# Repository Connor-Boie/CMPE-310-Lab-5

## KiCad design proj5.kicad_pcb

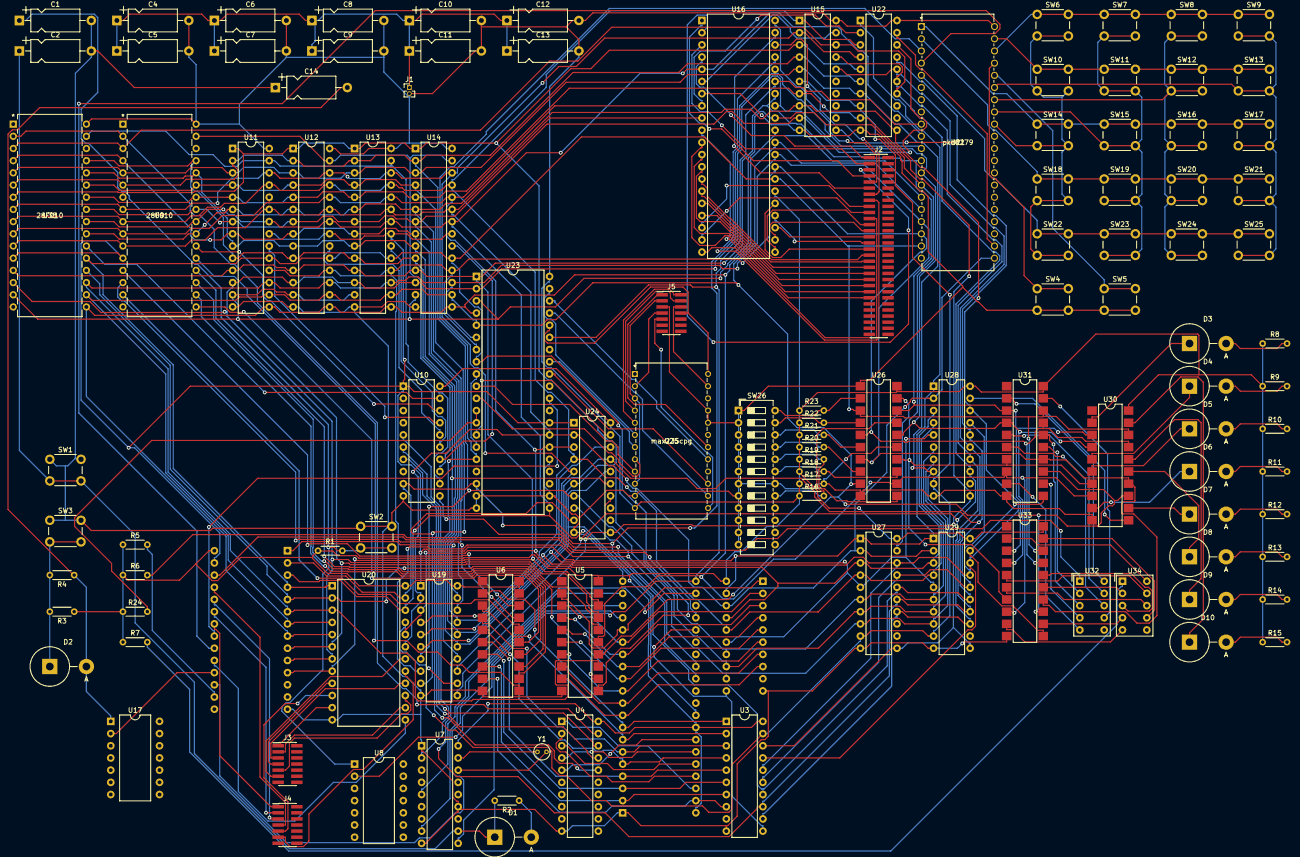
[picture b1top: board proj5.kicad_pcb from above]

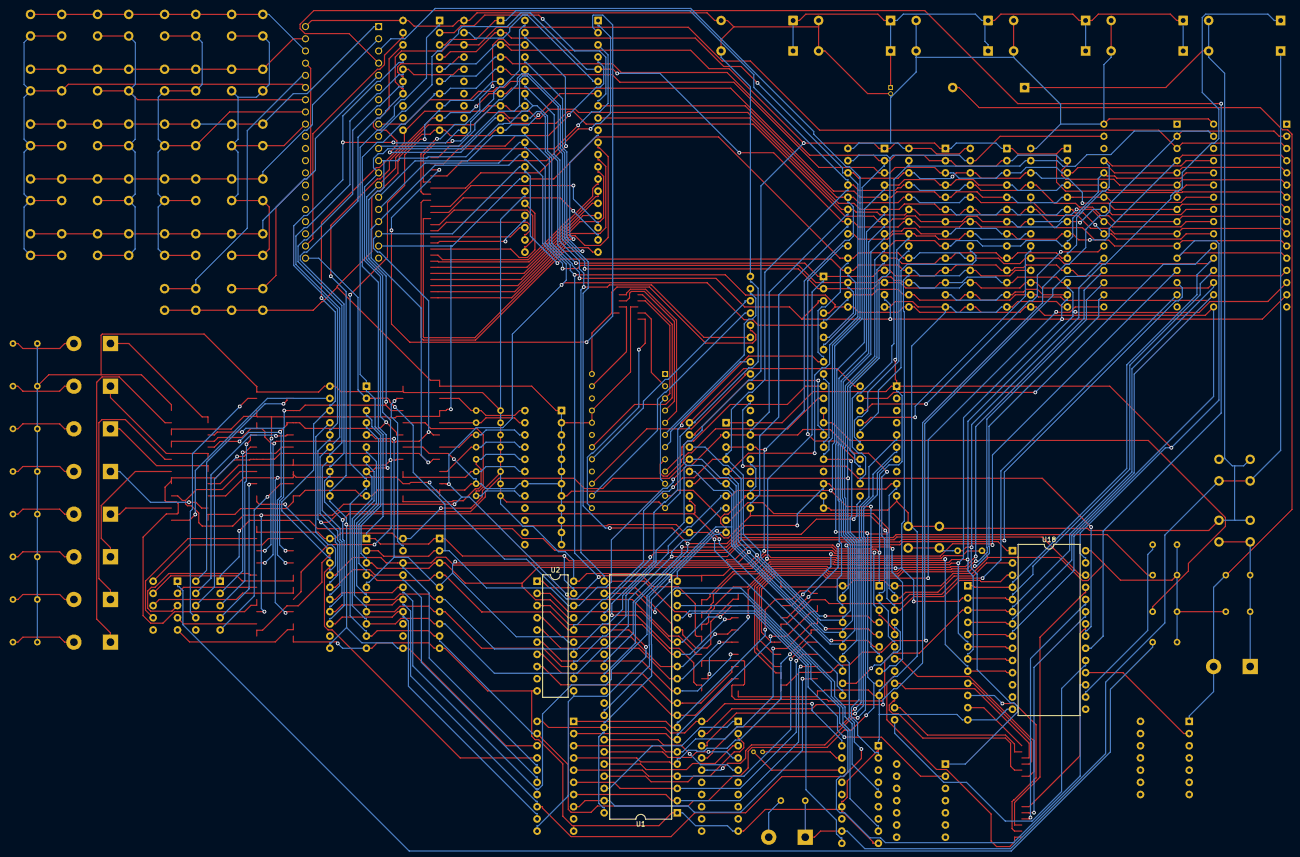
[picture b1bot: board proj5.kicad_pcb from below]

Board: 2 copper layers, 114 parts (3 on the bottom side), 204 nets.

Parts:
C1, C2: C; CP_Axial_L10.0mm_D4.5mm_P15.00mm_Horizontal
C4, C5, C6, C7, C8, C9, C10, C11, C12, C13: 10uF; CP_Axial_L10.0mm_D4.5mm_P15.00mm_Horizontal
C14: CP1_Small; CP_Axial_L10.0mm_D4.5mm_P15.00mm_Horizontal
D1, D2: DIODE; D_5KPW_P7.62mm_Vertical_AnodeUp
D3, D4, D5, D6, D7, D8, D9, D10: D5; D_5KPW_P7.62mm_Vertical_AnodeUp
J1: Conn_01x02; PinHeader_1x02_P1.27mm_Vertical
J2: Conn_02x30_Odd_Even; PinHeader_2x30_P1.27mm_Vertical_SMD
J3, J4, J5: Conn_02x07_Odd_Even; PinHeader_2x07_P1.27mm_Vertical_SMD
R1, R2: Resistor; R_Axial_DIN0204_L3.6mm_D1.6mm_P5.08mm_Horizontal
R3, R4, R5, R6, R7, R8, R9, R10, R11, R12, R13, R14, R15: R_Small_US; R_Axial_DIN0204_L3.6mm_D1.6mm_P5.08mm_Horizontal
R16: R1; R_Axial_DIN0204_L3.6mm_D1.6mm_P5.08mm_Horizontal
R17: R2; R_Axial_DIN0204_L3.6mm_D1.6mm_P5.08mm_Horizontal
R18: R3; R_Axial_DIN0204_L3.6mm_D1.6mm_P5.08mm_Horizontal
R19: R4; R_Axial_DIN0204_L3.6mm_D1.6mm_P5.08mm_Horizontal
R20: R5; R_Axial_DIN0204_L3.6mm_D1.6mm_P5.08mm_Horizontal
R21: R6; R_Axial_DIN0204_L3.6mm_D1.6mm_P5.08mm_Horizontal
R22: R7; R_Axial_DIN0204_L3.6mm_D1.6mm_P5.08mm_Horizontal
R23: R8; R_Axial_DIN0204_L3.6mm_D1.6mm_P5.08mm_Horizontal
R24: 10k; R_Axial_DIN0204_L3.6mm_D1.6mm_P5.08mm_Horizontal
SW1, SW2, SW3, SW4, SW5, SW6, SW7, SW8, SW9, SW10, SW11, SW12, SW13, SW14, SW15, SW16, SW17, SW18, SW19, SW20, SW21, SW22, SW23, SW24, SW25: SW_Push; SW_PUSH_6mm_H5mm
SW26: SW_DIP_x12; SW_DIP_SPSTx12_Slide_6.7x32.04mm_W7.62mm_P2.54mm_LowProfile
U1: 8086_Min_Mode; DIP-40_W15.24mm
U2, U3, U4, U10, U15, U19, U22, U24, U27, U28, U29: PAL16L8; DIP-20_W7.62mm
U5, U6: 74LS245; SMDIP-20_W7.62mm
U7: 8284; DIP-18_W7.62mm
U8, U17: 74LS14; DIP-14_W10.16mm
U9, U35: 28F010
U11, U12, U13, U14: CY7C199; DIP-28_W7.62mm
U16: 8255; DIP-40_W15.24mm
U18: 8259A; DIP-28_W15.24mm
U20: 8254; DIP-24_W15.24mm
U21: pkd8279
U23: 16550; DIP-40_W15.24mm
U25: max235cpg
U26: 74LS244; SMDIP-20_W7.62mm
U30, U31, U33: 74LS374; SMDIP-20_W7.62mm
U32, U34: HDSP-7401
Y1: Crystal; Crystal_C38-LF_D3.0mm_L8.0mm_Vertical

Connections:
/CLK0: J3.7, U20.9
/CLK1: J3.9, U20.15
/CLK2: J3.11, U20.18
/G0: J3.1, U20.11
/G1: J3.3, U20.14
/G2: J3.5, U20.16
/IR1: U18.19, U20.13
/IR4: J4.1, U18.22
/IR5: J4.3, U18.23
/IR6: J4.5, U18.24
/IR7: J4.7, U18.25
/OUT0: J4.9, U20.10
/OUT2: J4.11, U20.17
A0: U2.19, U9.12, U10.1, U11.21, U12.21, U13.21, U14.21, U18.27, U19.1, U22.1, U23.28, U24.1, U27.1, U28.1, U29.1, U35.12
A1: U2.18, U9.11, U11.23, U12.23, U13.23, U14.23, U16.9, U19.2, U20.19, U21.21, U23.27, U24.2, U27.2, U28.2, U29.2, U35.11
A2: U2.17, U9.10, U11.24, U12.24, U13.24, U14.24, U16.8, U19.3, U20.20, U22.2, U23.26, U24.3, U27.3, U28.3, U29.3, U35.10
A3: U2.16, U9.9, U11.25, U12.25, U13.25, U14.25, U15.1, U19.4, U22.3, U24.4, U27.4, U28.4, U29.4, U35.9
A4: U2.15, U9.8, U11.26, U12.26, U13.26, U14.26, U15.2, U19.5, U22.4, U24.5, U27.5, U28.5, U29.5, U35.8
A5: U2.14, U9.7, U11.1, U12.1, U13.1, U14.1, U15.3, U19.6, U22.5, U24.6, U27.6, U28.6, U29.6, U35.7
A6: U2.13, U9.6, U11.2, U12.2, U13.2, U14.2, U15.4, U19.7, U22.6, U24.7, U27.7, U28.7, U29.7, U35.6
A7: U2.12, U9.5, U11.3, U12.3, U13.3, U14.3, U15.5, U19.8, U22.7, U24.8, U27.8, U28.8, U29.8, U35.5
A8: U3.19, U9.27, U11.4, U12.4, U13.4, U14.4, U15.6, U19.9, U22.8, U24.9, U27.9, U28.9, U29.9, U35.27
A9: U3.18, U9.26, U11.5, U12.5, U13.5, U14.5, U15.7, U19.11, U22.9, U24.11, U27.11, U28.11, U29.11, U35.26
A10: U3.17, U9.23, U11.6, U12.6, U13.6, U14.6, U15.8, U19.18, U22.11, U28.18, U29.18, U35.23
A11: U3.16, U9.25, U11.7, U12.7, U13.7, U14.7, U15.9, U19.17, U22.18, U24.18, U27.18, U28.17, U29.17, U35.25
A12: U3.15, U9.4, U11.8, U12.8, U13.8, U14.8, U15.11, U19.16, U22.17, U24.17, U27.17, U28.16, U29.16, U35.4
A13: U3.14, U9.28, U11.9, U12.9, U13.9, U14.9, U15.16, U19.15, U22.16, U24.16, U27.16, U28.15, U29.15, U35.28
A14: U3.13, U9.29, U11.10, U12.10, U13.10, U14.10, U15.17, U19.14, U22.15, U24.15, U27.15, U28.14, U29.14, U35.29
A15: U3.12, U9.3, U15.18, U19.13, U22.14, U24.14, U27.14, U28.13, U29.13, U35.3
A16: U4.19, U9.2, U35.2
A17: U4.18, U10.5
A18: U4.17, U10.6
A19: U4.16, U10.7
AD0: U1.16, U2.1, U5.2
AD1: U1.15, U2.2, U5.3
AD2: U1.14, U2.3, U5.4
AD3: U1.13, U2.4, U5.5
AD4: U1.12, U2.5, U5.6
AD5: U1.11, U2.6, U5.7
AD6: U1.10, U2.7, U5.8
AD7: U1.9, U2.8, U5.9
AD8: U1.8, U3.1, U6.2
AD9: U1.7, U3.2, U6.3
AD10: U1.6, U3.3, U6.4
AD11: U1.5, U3.4, U6.5
AD12: U1.4, U3.5, U6.6
AD13: U1.3, U3.6, U6.7
AD14: U1.2, U3.7, U6.8
AD15: U1.39, U3.8, U6.9
CE1: U10.19, U35.22
CE2: U9.22, U10.18
CE3: U10.17, U11.20
CE4: U10.16, U12.20
CE5: U10.15, U13.20
CE6: U10.14, U14.20
CLK: U29.19, U31.11, U33.11
CTS: J5.8, U23.36, U25.24
Col0: SW6.2, SW10.2, SW14.2, SW18.2, SW22.2, U21.32
Col1: SW7.2, SW11.2, SW15.2, SW19.2, SW23.2, U21.33
Col2: SW8.2, SW12.2, SW16.2, SW20.2, SW24.2, U21.34
Col3: SW9.2, SW13.2, SW17.2, SW21.2, SW25.2, U21.35
D0: U5.18, U11.11, U12.11, U13.11, U14.11, U16.34, U18.11, U20.8, U21.12, U23.1, U26.18, U30.3, U31.3, U33.3, U35.13
D1: U5.17, U11.12, U12.12, U13.12, U14.12, U16.33, U18.10, U20.7, U21.13, U23.2, U26.16, U30.4, U31.4, U33.4, U35.14
D2: U5.16, U11.13, U12.13, U13.13, U14.13, U16.32, U18.9, U20.6, U21.14, U23.3, U26.14, U30.7, U31.7, U33.7, U35.15
D3: U5.15, U11.15, U12.15, U13.15, U14.15, U16.31, U18.8, U20.5, U21.15, U23.4, U26.12, U30.8, U31.8, U33.8, U35.17
D4: U5.14, U11.16, U12.16, U13.16, U14.16, U16.30, U18.7, U20.4, U21.16, U23.5, U26.9, U30.13, U31.13, U33.13, U35.18
D5: U5.13, U11.17, U12.17, U13.17, U14.17, U16.29, U18.6, U20.3, U21.17, U23.6, U26.7, U30.14, U31.14, U33.14, U35.19
D6: U5.12, U11.18, U12.18, U13.18, U14.18, U16.28, U18.5, U20.2, U21.18, U23.7, U26.5, U30.17, U31.17, U33.17, U35.20
D7: U5.11, U11.19, U12.19, U13.19, U14.19, U16.27, U18.4, U20.1, U21.19, U23.8, U26.3, U30.18, U31.18, U33.18, U35.21
D8: U6.18, U9.13
D9: U6.17, U9.14
D10: U6.16, U9.15
D11: U6.15, U9.17
D12: U6.14, U9.18
D13: U6.13, U9.19
D14: U6.12, U9.20
D15: U6.11, U9.21
DCD: J5.1, U25.18
DSR: J5.6, U25.23
DTR: U23.33, U25.7
DTR9: J5.4, U25.4
GND: C1.2, C2.2, C14.1, J5.5, R17.2, SW1.1, SW2.1, SW3.1, SW4.2, SW5.2, SW26.1, SW26.2, SW26.3, SW26.4, SW26.5, SW26.6, SW26.7, SW26.8, SW26.9, SW26.10, SW26.11, SW26.12, SW26.18, U1.1, U1.20, U2.10, U3.10, U4.10, U5.10, U6.10, U7.1, U7.9, U7.13, U10.10, U11.14, U12.14, U13.14, U14.14, U15.10, U16.7, U18.14, U19.10, U20.12, U22.10, U23.19, U23.20, U23.22, U23.25, U24.10, U25.11, U25.20, U25.21, U26.1, U26.10, U26.15, U27.10, U28.10, U29.10, U30.10, U31.10, U33.10
HWR: U9.31, U10.13, U12.27, U14.27
INTA: U1.24, U18.26
INTR: U1.18, U18.17
INTR16550: U18.21, U23.30
IRQ: U18.20, U21.4
LWR: U10.12, U11.27, U13.27, U35.31
M\IO: U1.28, U10.11
unnamed: C1.1, R1.2, SW2.2, U8.1
unnamed: C2.1, D1.1, R2.2, SW1.2, U7.11
unnamed: C4.1, C5.1, C6.1, C7.1, C8.1, C9.1, C10.1, C11.1, C12.1, C13.1, J1.1
unnamed: C14.2, D2.2, R4.1, U17.1
unnamed: D1.2, R2.1
unnamed: D2.1, R3.2, R4.2, SW3.2
unnamed: D3.1, U30.2
unnamed: D3.2, R8.2
unnamed: D4.1, U30.5
unnamed: D4.2, R9.2
unnamed: D5.1, U30.6
unnamed: D5.2, R10.2
unnamed: D6.1, U30.9
unnamed: D6.2, R11.2
unnamed: D7.1, U30.12
unnamed: D7.2, R12.2
unnamed: D8.1, U30.15
unnamed: D8.2, R13.2
unnamed: D9.1, U30.16
unnamed: D9.2, R14.2
unnamed: D10.1, U30.19
unnamed: D10.2, R15.2
unnamed: R5.2, U18.16
unnamed: R6.2, U32.1
unnamed: R7.2, U34.1
unnamed: R16.2, SW26.17, U26.17
unnamed: R18.2, SW26.19, U26.13
unnamed: R19.2, SW26.20, U26.11
unnamed: R20.2, SW26.21, U26.8
unnamed: R21.2, SW26.22, U26.6
unnamed: R22.2, SW26.23, U26.4
unnamed: R23.2, SW26.24, U26.2
unnamed: R24.2, U23.12, U23.13
unnamed: SW4.1, U21.37
unnamed: SW5.1, U21.36
unnamed: U1.17, U8.2
unnamed: U1.19, U7.8
unnamed: U1.25, U2.11, U3.11
unnamed: U1.34, U4.5
unnamed: U1.35, U4.4
unnamed: U1.36, U4.3
unnamed: U1.37, U4.2
unnamed: U1.38, U4.1
unnamed: U7.16, Y1.2
unnamed: U7.17, Y1.1
unnamed: U15.19, U16.6
unnamed: U17.2, U18.18
unnamed: U18.1, U19.19
unnamed: U19.12, U20.21
unnamed: U21.22, U22.19
unnamed: U23.14, U24.19
unnamed: U23.9, U23.15
unnamed: U26.19, U27.19
unnamed: U28.19, U30.11
unnamed: U31.2, U32.10
unnamed: U31.5, U32.9
unnamed: U31.6, U32.8
unnamed: U31.9, U32.5
unnamed: U31.12, U32.4
unnamed: U31.15, U32.2
unnamed: U31.16, U32.3
unnamed: U31.19, U32.7
unnamed: U33.2, U34.10
unnamed: U33.5, U34.9
unnamed: U33.6, U34.8
unnamed: U33.9, U34.5
unnamed: U33.12, U34.4
unnamed: U33.15, U34.2
unnamed: U33.16, U34.3
unnamed: U33.19, U34.7
P0: J2.1, U16.4
P1: J2.3, U16.3
P2: J2.5, U16.2
P3: J2.7, U16.1
P4: J2.9, U16.40
P5: J2.11, U16.39
P6: J2.13, U16.38
P7: J2.15, U16.37
P8: J2.17, U16.18
P9: J2.19, U16.19
P10: J2.21, U16.20
P11: J2.23, U16.21
P12: J2.25, U16.22
P13: J2.27, U16.23
P14: J2.29, U16.24
P15: J2.31, U16.25
P16: J2.33, U16.14
P17: J2.35, U16.15
P18: J2.37, U16.16
P19: J2.39, U16.17
P20: J2.41, U16.13
P21: J2.43, U16.12
P22: J2.45, U16.11
P23: J2.47, U16.10
PCLK: U7.2, U21.3, U23.16
R1: J5.9, U25.13
R1OUT: U23.10, U25.9
R2OUT: U23.39, U25.6
R4OUT: U23.38, U25.17
R5OUT: U23.37, U25.14
RD: U1.32, U9.24, U11.22, U12.22, U13.22, U14.22, U16.5, U18.3, U20.22, U21.10, U23.21, U35.24
READY: U1.22, U7.5
RTS: U23.32, U25.15
RTS9: J5.7, U25.2
RXD: J5.2, U25.5
Reset: U1.21, U7.10, U16.35, U21.9, U23.35
Row0: SW6.1, SW7.1, SW8.1, SW9.1, U21.38
Row1: SW10.1, SW11.1, SW12.1, SW13.1, U21.39
Row2: SW14.1, SW15.1, SW16.1, SW17.1, U21.1
Row3: SW18.1, SW19.1, SW20.1, SW21.1, U21.2
Row4: SW22.1, SW23.1, SW24.1, SW25.1, U21.5
SOUT: U23.11, U25.8
TDX: J5.3, U25.3, U25.10
VCC: C4.2, C5.2, C6.2, C7.2, C8.2, C9.2, C10.2, C11.2, C12.2, C13.2, J1.2, R1.1, R3.1, R5.1, R6.1, R7.1, R8.1, R9.1, R10.1, R11.1, R12.1, R13.1, R14.1, R15.1, R16.1, R17.1, R18.1, R19.1, R20.1, R21.1, R22.1, R23.1, R24.1, U1.33, U1.40, U2.20, U3.20, U4.20, U5.20, U6.20, U7.18, U9.32, U10.20, U11.28, U12.28, U13.28, U14.28, U15.20, U16.26, U18.28, U19.20, U20.24, U21.40, U22.20, U23.40, U24.20, U25.12, U26.20, U27.20, U28.20, U29.20, U30.20, U31.20, U33.20, U35.32
WR: U1.29, U10.9, U16.36, U18.2, U20.23, U21.11, U23.18

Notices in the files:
parts and their libraries:
Copyright 2016 Accelerated Designs. All rights reserved.
